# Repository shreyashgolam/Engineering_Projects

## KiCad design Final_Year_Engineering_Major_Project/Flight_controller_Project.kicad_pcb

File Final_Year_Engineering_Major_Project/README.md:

# Flight Controller PCB Design Using KiCad

## Project Overview
This project involves designing a **Flight Controller PCB** using **KiCad**. The PCB is intended for drone and UAV applications, providing essential functionalities like sensor integration, power management, and communication interfaces for flight control.

## System Architecture
The PCB consists of multiple modules interconnected for efficient data processing and motor control:

- **Microcontroller Unit (MCU)**:
  - STM32H753VITx (Flight Control Computer - FCC)
  - STM32F405RGTx (Navigation Computer - NAVC)
- **Power Management**:
  - 3.3V and 5V voltage regulators
  - Battery monitoring and current sensing (INA219AIDCNR)
  - Reverse polarity protection
- **Communication Interfaces**:
  - I2C, SPI, UART
  - USB debugging and programming
  - CAN bus (future expansion)
- **Sensor Integration**:
  - Inertial Measurement Unit (IMU) - BMI088
  - Magnetometer - IIS2MDCTR
  - Barometer - MPRLS0025PA00001A
  - GPS Receiver - u-blox MAX-8Q
  - Temperature Sensor - TMP100
- **Peripheral Control**:
  - PWM outputs for ESC/motor control
  - General-purpose GPIOs for expansion
  - Debugging LEDs and status indicators

## PCB Design
- **Schematic Files**:
  - `FCC.kicad_sch` - Flight Control Computer
  - `NAVC.kicad_sch` - Navigation Computer
  - `FCCPeripherals.kicad_sch` - Flight Control Peripherals
  - `NAVCPeripherals.kicad_sch` - Navigation Peripherals
  - `Power.kicad_sch` - Power Distribution
  - `Connections.kicad_sch` - Interconnects and external interfaces
- **PCB Layout File**:
  - `Flight_controller_Project.kicad_pcb`
- **Manufacturing Files**:
  - Gerber files and drill files for PCB fabrication
  - BOM (`.csv/.xml`) for component listing

## Workflow
1. **Schematic Design** – Define circuit connections in KiCad.
2. **PCB Layout** – Optimize routing and placement for minimal interference.
3. **Gerber File Generation** – Export necessary manufacturing files.
4. **Fabrication & Assembly** – Order PCBs and assemble components.
5. **Testing & Debugging** – Verify power, communication, and sensor readings.
6. **Firmware Development** – Program MCU for flight control operations.

## Applications
- Autonomous UAV and drone flight control
- GPS-based navigation systems
- Sensor fusion and real-time data processing
- Research and prototyping of flight stabilization algorithms

## Future Enhancements
- Implement CAN bus communication for robust inter-device connectivity.
- Integrate additional sensors for improved stability and performance.
- Develop an RF-based remote control module for manual override.
- Optimize power management for extended battery life.

This project provides a deep understanding of **flight electronics, embedded systems, and PCB design**.

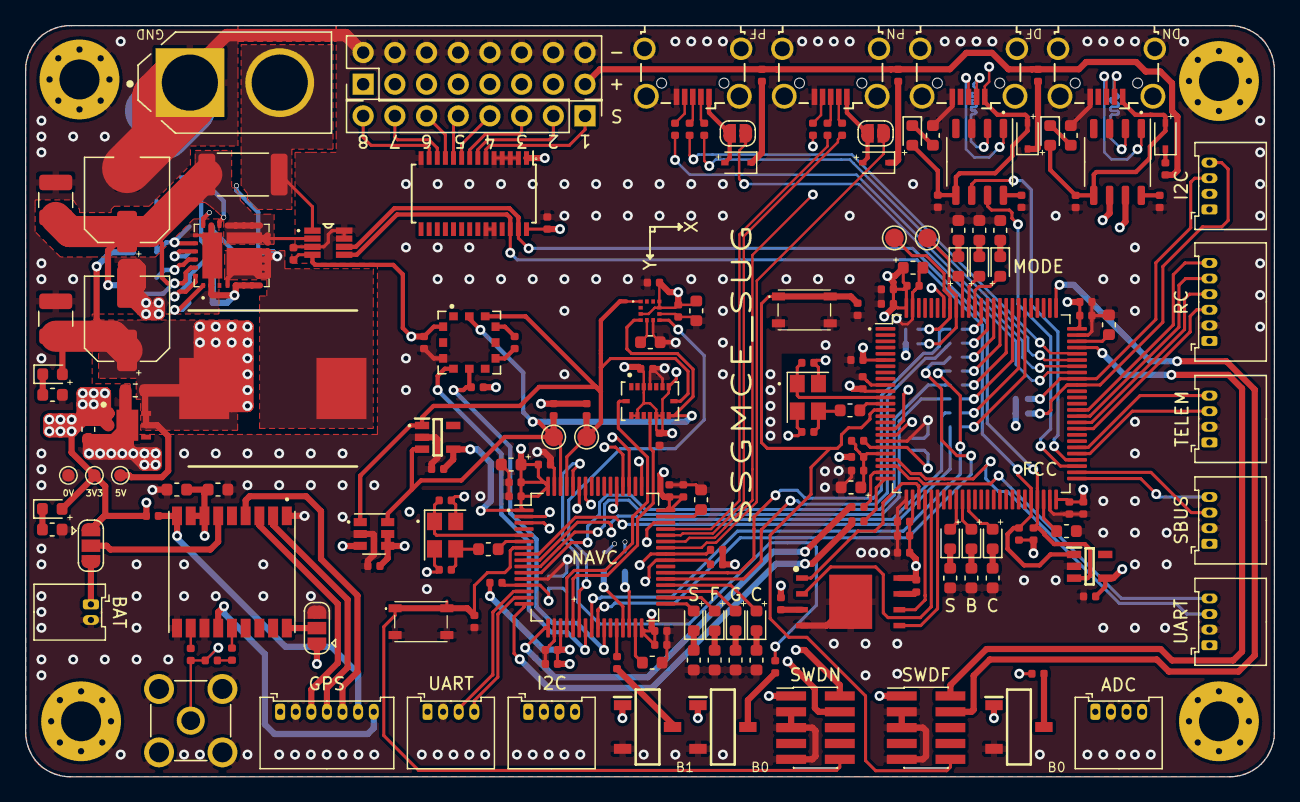
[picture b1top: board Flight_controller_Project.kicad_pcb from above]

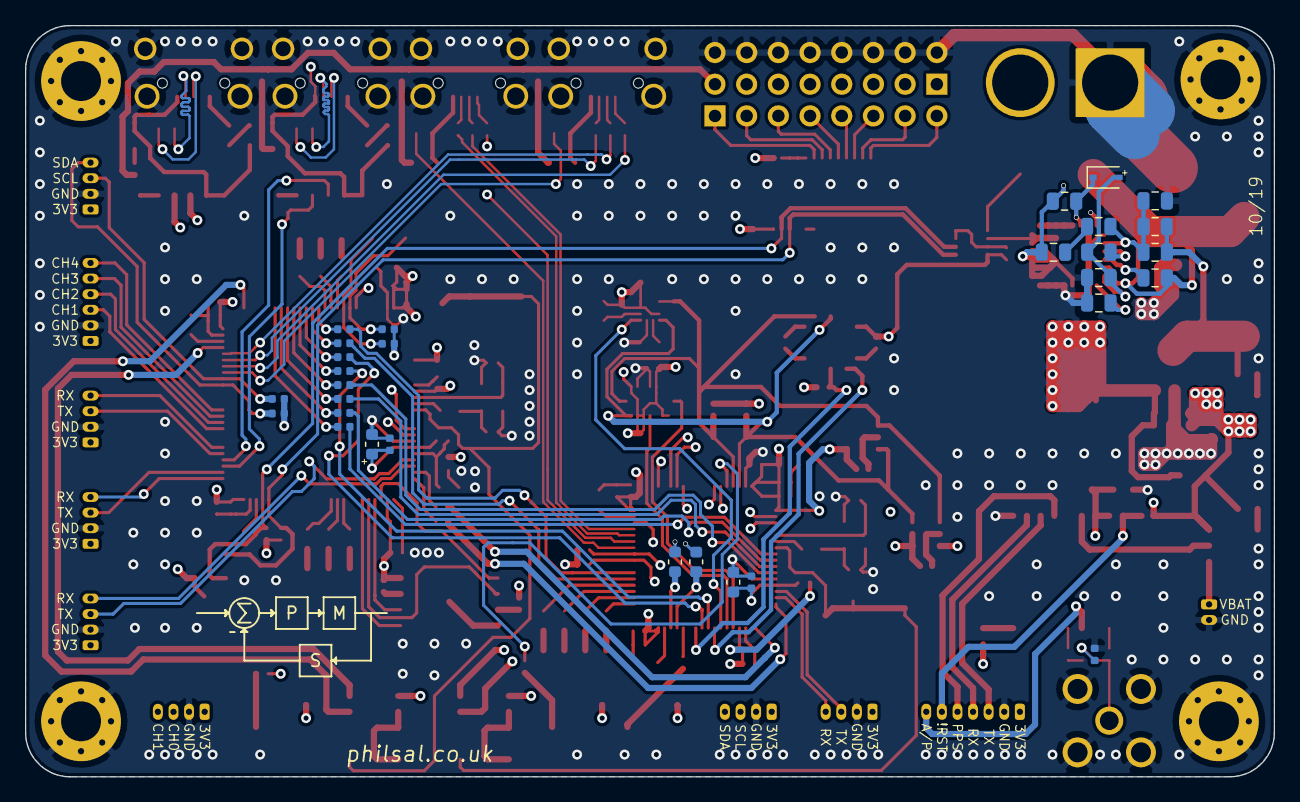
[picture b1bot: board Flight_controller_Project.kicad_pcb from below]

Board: 4 copper layers, 100.1 x 60.2 mm, 211 parts (30 on the bottom side), 174 nets.

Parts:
5V, 5V#2, 5V#3: TestPoint_Pad_D1.0mm
ADC: Conn_01x04; Molex_PicoBlade_53048-0410_1x04_P1.25mm_Horizontal
ANT1: 5-1814832-1; TE_5-1814832-1
BAT: Conn_01x02; Molex_PicoBlade_53048-0210_1x02_P1.25mm_Horizontal
BAT1: XT60-M; AMASS_XT60-M
C1, C8: 100u; C_Elec_6.3x7.7
C2, C9: 47u; C_1210_3225Metric
C3, C4: 2u2; C_0805_2012Metric
C5, C6: 100n; C_0805_2012Metric
C7: 4n7; C_0805_2012Metric
C10, C16, C17, C18, C19, C20, C21, C22, C23, C24, C25, C26, C28, C30, C31, C34, C35, C36, C40, C41, C42, C43, C44, C45, C46, C47, C48, C49, C51, C54, C55, C56, C58, C60, C61, C63, C68, C69, C70, C71: 100n; C_0402_1005Metric
C11, C12, C15, C39, C62: 10u; C_0603_1608Metric
C13, C14, C37, C38: 2u2; C_0603_1608Metric
C27, C29, C50, C64, C65: 1u; C_0603_1608Metric
C32, C33, C52, C53: 10p; C_0402_1005Metric
C57: 1n; C_0402_1005Metric
C59: 220n; C_0603_1608Metric
C66: 22p; C_0402_1005Metric
C67: 10n; C_0402_1005Metric
D1, D2, D3, D4, D5: SD103AWS; D_SOD-323
FB1, FB2, FB3, FB4, FB5, FB6: Ferrite_Bead_Small; L_0402_1005Metric
FCC: STM32H753VITx; LQFP-100_14x14mm_P0.5mm
GPS: Conn_01x07; Molex_PicoBlade_53048-0710_1x07_P1.25mm_Horizontal
HSE1, HSE2: 25MHz; Crystal_SMD_Abracon_ABM8G-4Pin_3.2x2.5mm
I2C, I2C#2: Conn_01x04; Molex_PicoBlade_53048-0410_1x04_P1.25mm_Horizontal
JP1, JP2: SolderJumper_2_Open; SolderJumper-2_P1.3mm_Open_RoundedPad1.0x1.5mm
JP3: SolderJumper_3_Open; SolderJumper-3_P1.3mm_Open_RoundedPad1.0x1.5mm
JP4: Jumper_3_Open; SolderJumper-3_P1.3mm_Open_RoundedPad1.0x1.5mm
L1: 15u; INDPM135125X650N
L2: 27n; L_0402_1005Metric
LED1, LED2, LED13, LED14: G; LED_0603_1608Metric
LED3, LED4, LED9, LED10: R; LED_0603_1608Metric
LED5, LED11: Y; LED_0603_1608Metric
LED6, LED7, LED8, LED12: B; LED_0603_1608Metric
NAVC: STM32F405RGTx; LQFP-64_10x10mm_P0.5mm
PWM_POW1: Conn_02x08_Odd_Even; PinHeader_2x08_P2.54mm_Vertical
PWM_SIG1: 2.54mm; PinHeader_1x08_P2.54mm_Vertical
R1: 0.01; R_2512_6332Metric
R2, R3: 10k; R_0805_2012Metric
R4: 19k6; R_0805_2012Metric
R5: 6k8; R_0805_2012Metric
R6: 1k3; R_0805_2012Metric
R7, R58, R59: 560; R_0603_1608Metric
R8: 240; R_0603_1608Metric
R9, R10, R11, R12, R13, R14, R28, R29, R30, R31: 4k7; R_0402_1005Metric
R15, R16, R17, R33, R34, R35: 330; R_0603_1608Metric
R18, R19, R20, R36: 100; R_0603_1608Metric
R21: 47; R_0402_1005Metric
R22, R24, R25, R26, R27, R37, R38: 10k; R_0402_1005Metric
R23, R32: 620; R_0603_1608Metric
R39, R40, R41, R42, R43, R44, R45, R46, R47, R48, R49: 10; R_0402_1005Metric
R50, R51: 0; R_0603_1608Metric
R52, R53, R55, R56: 22; R_0402_1005Metric
R54, R57: 560; R_0402_1005Metric
RC: Conn_01x06; Molex_PicoBlade_53048-0610_1x06_P1.25mm_Horizontal
REG1: MIC26903YJL-TR; MIC24054YJLTR
REG2: LD39200PU33R; SON95P300X300X100-7N-D
SBUS: Conn_01x04; Molex_PicoBlade_53048-0410_1x04_P1.25mm_Horizontal
SW1, SW5: SKRPANE010; SKRPADE010
SW2, SW3, SW4: TDD01H0SB1R; SOT175P420X230-3N
SWDF: Conn_02x05_Odd_Even; PinHeader_2x05_P1.27mm_Vertical_SMD
SWDN: Conn_02x05_Odd_Even; PinHeader_2x05_P1.27mm_Vertical_SMD
TELEM: Conn_01x04; Molex_PicoBlade_53048-0410_1x04_P1.25mm_Horizontal
TP1, TP2, TP3, TP4: I2C1; TestPoint_Pad_D1.5mm
U1: INA219AIDCNR; SOT65P280X145-8N
U2: PCA9685PW; TSSOP-28_4.4x9.7mm_P0.65mm
U3, U9: 24CW1280T-I_OT; SOT95P280X145-5N
U4: W25N01GVZEIG_TR; SON127P800X600X80-9N-D
U5: BMI088; PQFN50P450X300X100-16N
U6: TMP100; SOT-23-6
U7: MPRLS0025PA00001A; XDCR_MPRLS0025PA00001A
U8: IIS2MDCTR
U10: u-blox MAX-8Q; GPS18P-SMD-1.1-10X9.6MM
U11, U12: otter:CH330; SSOP-8_3.9x5.05mm_P1.27mm
UART: Conn_01x04; Molex_PicoBlade_53048-0410_1x04_P1.25mm_Horizontal
UART#2: Conn_01x04; Molex_PicoBlade_53048-0410_1x04_P1.25mm_Horizontal
USB1, USB2, USB3, USB4: USB_B_Micro; USB_Micro-B_Wuerth_629105150521_CircularHoles

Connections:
+3V3: 5V#2.1, ADC.1, C10.1, C12.1, C15.1, C16.1, C17.1, C18.1, C19.1, C20.1, C21.1, C22.1, C23.1, C24.1, C25.1, C26.1, C34.1, C35.1, C36.2, C39.1, C40.1, C41.1, C42.1, C43.1, C44.1, C45.1, C46.1, C47.1, C48.1, C54.1, C55.1, C56.1, C58.1, C60.1, C61.1, C62.1, C63.1, C64.1, C65.1, FB1.2, FB2.2, FCC.6, FCC.11, FCC.27, FCC.50, FCC.75, FCC.100, GPS.1, I2C.1, I2C#2.1, JP3.1, JP4.1, LED2.2, NAVC.1, NAVC.19, NAVC.32, NAVC.48, NAVC.64, R9.1, R10.1, R11.1, R12.1, R13.1, R14.1, R24.1, R25.1, R28.1, R29.1, R30.1, R31.1, R37.1, R38.1, RC.1, REG2.1, REG2.2, SBUS.1, SW2.1, SW3.1, SW4.1, SWDF.1, SWDN.1, TELEM.1, U1.4, U2.1, U2.28, U3.4, U4.8, U5.3, U5.7, U5.10, U5.11, U5.14, U5.15, U6.3, U6.4, U6.5, U7.12, U8.3, U8.9, U8.10, U9.4, U10.7, U10.8, UART.1, UART#2.1
+5V: 5V.1, C7.1, C8.1, C9.1, C11.1, FB3.1, FB4.1, FB5.1, FB6.1, L1.2, LED1.2, PWM_POW1.1, PWM_POW1.3, PWM_POW1.5, PWM_POW1.7, PWM_POW1.9, PWM_POW1.11, PWM_POW1.13, PWM_POW1.15, R5.1, REG2.5, REG2.6
ADC3_0_FCC: ADC.3, FCC.17
ADC3_1_FCC: ADC.4, FCC.18
BAR_NRST_NAVC: NAVC.26, R37.2, U7.8
BOOT0_FCC: FCC.94, R22.2
BOOT0_NAVC: NAVC.60, R26.2
BOOT1_NAVC: NAVC.28, R27.2
GND: 5V#3.1, ADC.2, ANT1.2, ANT1.3, ANT1.4, ANT1.5, BAT.2, BAT1.1, C1.2, C2.2, C3.2, C4.2, C8.2, C9.2, C10.2, C11.2, C12.2, C13.2, C14.2, C15.2, C16.2, C17.2, C18.2, C19.2, C20.2, C21.2, C22.2, C23.2, C24.2, C25.2, C26.2, C27.2, C28.2, C29.2, C30.2, C31.2, C32.2, C33.2, C34.2, C35.2, C36.1, C37.2, C38.2, C39.2, C40.2, C41.2, C42.2, C43.2, C44.2, C45.2, C46.2, C47.2, C48.2, C49.2, C50.2, C51.2, C52.2, C53.2, C54.2, C55.2, C56.2, C58.2, C59.2, C60.2, C61.2, C62.2, C63.2, C64.2, C65.2, C67.2, C68.1, C69.1, C70.1, C71.1, FCC.10, FCC.19, FCC.26, FCC.49, FCC.74, FCC.99, GPS.2, HSE1.2, HSE1.4, HSE2.2, HSE2.4, I2C.2, I2C#2.2, JP3.3, NAVC.12, NAVC.18, NAVC.63, PWM_POW1.2, PWM_POW1.4, PWM_POW1.6, PWM_POW1.8, PWM_POW1.10, PWM_POW1.12, PWM_POW1.14, PWM_POW1.16, R6.1, R7.1, R8.1, R15.1, R16.1, R17.1, R18.1, R19.1, R20.1, R33.1, R34.1, R35.1, R36.1, R58.1, R59.1, RC.2, REG1.2, REG1.5, REG1.6, REG1.7, REG1.8, REG1.21, REG1.23, REG1.31, REG2.3, REG2.7, SBUS.2, SW1.3, SW1.4, SW2.2, SW3.2, SW4.2, SW5.3, SW5.4, SWDF.3, SWDF.5, SWDF.9, SWDN.3, SWDN.5, SWDN.9, TELEM.2, U1.3, U1.7, U1.8, U2.2, U2.3, U2.4, U2.5, U2.14, U2.23, U2.24, U3.2, U4.4, U4.9, U5.4, U5.6, U6.2, U7.10, U8.6, U8.8, U9.2, U10.1, U10.10, U10.12, U11.3, U12.3, UART.2, UART#2.2, USB1.5, USB1.6, USB2.5, USB2.6, USB3.5, USB3.6, USB4.5, USB4.6
GPIO_A_FCC: FCC.81, R40.2
GPIO_A_NAVC: NAVC.8, R40.1
GPIO_B_FCC: FCC.82, R41.2
GPIO_B_NAVC: NAVC.9, R41.1
GPIO_C_FCC: FCC.83, R42.2
GPIO_C_NAVC: NAVC.10, R42.1
GPIO_D_FCC: FCC.84, R43.2
GPIO_D_NAVC: NAVC.11, R43.1
GPIO_E_FCC: FCC.85, R44.2
GPIO_E_NAVC: NAVC.24, R44.1
GPIO_F_FCC: FCC.86, R45.2
GPIO_F_NAVC: NAVC.25, R45.1
GPIO_G_FCC: FCC.87, R46.2
GPIO_G_NAVC: NAVC.37, R46.1
GPIO_H_FCC: FCC.88, R47.2
GPIO_H_NAVC: NAVC.38, R47.1
GPS_BAT_BACKUP: JP4.2, U10.6
GPS_LNA_EN_NAVC: GPS.7, NAVC.2, U10.13
GPS_NRST_NAVC: GPS.6, NAVC.3, R38.2, U10.9
GPS_PPS_NAVC: GPS.5, NAVC.53, U10.4
HSE_IN_FCC: C32.1, FCC.12, HSE1.1
HSE_IN_NAVC: C52.1, HSE2.1, NAVC.5
HSE_OUT_FCC: FCC.13, R23.1
HSE_OUT_NAVC: NAVC.6, R32.1
I2C1_SCL_FCC: FCC.92, R9.2, R50.2, TP1.1
I2C1_SCL_NAVC: NAVC.61, R28.2, TP3.1, U5.8, U6.1, U7.3, U8.1, U9.1
I2C1_SDA_FCC: FCC.93, R10.2, R51.2, TP2.1
I2C1_SDA_NAVC: NAVC.62, R29.2, TP4.1, U5.9, U6.6, U7.2, U8.4, U9.3
I2C2_SCL_FCC: FCC.46, R11.2, U1.5, U2.26, U3.1
I2C2_SCL_NAVC: NAVC.29, R50.1
I2C2_SDA_FCC: FCC.47, R12.2, U1.6, U2.27, U3.3
I2C2_SDA_NAVC: NAVC.30, R51.1
I2C3_SCL_FCC: FCC.67, I2C.3, R13.2
I2C3_SCL_NAVC: I2C#2.3, NAVC.41, R30.2
I2C3_SDA_FCC: FCC.66, I2C.4, R14.2
I2C3_SDA_NAVC: I2C#2.4, NAVC.40, R31.2
INT_ACC_NAVC: NAVC.20, U5.16
INT_BAR_NAVC: NAVC.23, U7.9
INT_GYR_NAVC: NAVC.21, U5.12
INT_MAG_NAVC: NAVC.22, U8.7
LED_A_FCC: FCC.34, LED3.2
LED_A_NAVC: LED9.2, NAVC.33
LED_B_FCC: FCC.35, LED4.2
LED_B_NAVC: LED10.2, NAVC.34
LED_C_FCC: FCC.36, LED5.2
LED_C_NAVC: LED11.2, NAVC.35
LED_D_FCC: FCC.89, LED6.2
LED_D_NAVC: LED12.2, NAVC.36
LED_E_FCC: FCC.90, LED7.2
LED_F_FCC: FCC.91, LED8.2
NRST_FCC: C31.1, FCC.14, SW1.1, SW1.2, SWDF.10
NRST_NAVC: C49.1, NAVC.7, SW5.1, SW5.2, SWDN.10
unnamed: ANT1.1, C66.1, C67.1, L2.2
unnamed: C3.1, REG1.1
unnamed: C4.1, D1.2, R3.2, REG1.28
unnamed: C6.2, R4.1
unnamed: C13.1, FCC.48
unnamed: C14.1, FCC.73
unnamed: C33.1, HSE1.3, R23.2
unnamed: C37.1, NAVC.31
unnamed: C38.1, NAVC.47
unnamed: C53.1, HSE2.3, R32.2
unnamed: C57.1, U7.6
unnamed: C57.2, U7.4
unnamed: C59.1, U8.5
unnamed: C66.2, U10.11
unnamed: C68.2, D4.2, LED13.2, U11.5, USB3.1
unnamed: C69.2, U11.8
unnamed: C70.2, D5.2, LED14.2, U12.5, USB4.1
unnamed: C71.2, U12.8
unnamed: D2.1, FB3.2
unnamed: D2.2, JP1.1, USB1.1
unnamed: D3.1, FB4.2
unnamed: D3.2, JP2.1, USB2.1
unnamed: D4.1, FB5.2
unnamed: D5.1, FB6.2
unnamed: BAT.1, JP4.3
unnamed: JP3.2, U10.18
unnamed: L2.1, R39.1
unnamed: LED1.1, R7.2
unnamed: LED2.1, R8.2
unnamed: LED3.1, R15.2
unnamed: LED4.1, R16.2
unnamed: LED5.1, R17.2
unnamed: LED6.1, R18.2
unnamed: LED7.1, R19.2
unnamed: LED8.1, R20.2
unnamed: LED9.1, R33.2
unnamed: LED10.1, R34.2
unnamed: LED11.1, R35.2
unnamed: LED12.1, R36.2
unnamed: LED13.1, R58.2
unnamed: LED14.1, R59.2
unnamed: R22.1, SW2.3
unnamed: R24.2, U4.7
unnamed: R25.2, U4.3
unnamed: R26.1, SW3.3
unnamed: R27.1, SW4.3
unnamed: R39.2, U10.14
unnamed: R52.2, USB1.3
unnamed: R53.2, USB1.2
unnamed: R54.2, USB1.4
unnamed: R55.2, USB2.3
unnamed: R56.2, USB2.2
unnamed: R57.2, USB2.4
unnamed: U11.1, USB3.3
unnamed: U11.2, USB3.2
unnamed: U12.1, USB4.3
unnamed: U12.2, USB4.2
PWM_0: PWM_SIG1.1, U2.6
PWM_1: PWM_SIG1.2, U2.7
PWM_2: PWM_SIG1.3, U2.8
PWM_3: PWM_SIG1.4, U2.9
PWM_4: PWM_SIG1.5, U2.10
PWM_5: PWM_SIG1.6, U2.11
PWM_6: PWM_SIG1.7, U2.12
PWM_7: PWM_SIG1.8, U2.13
REG_BST: C5.2, D1.1, REG1.20
REG_CS: C5.1, C6.1, L1.1, REG1.4, REG1.9, REG1.10, REG1.11, REG1.12, REG1.22, REG1.29
REG_EN: R2.2, REG1.26
REG_FB: C7.2, R4.2, R5.2, R6.2, REG1.24
REG_PG: R3.1, REG1.25
REG_VIN: C1.1, C2.1, R1.1, R2.1, REG1.13, REG1.14, REG1.15, REG1.16, REG1.17, REG1.18, REG1.19, REG1.27, REG1.30, U1.2
SPI1_CS_FLASH_FCC: FCC.28, U4.1
SPI1_MISO_FCC: FCC.30, U4.2
SPI1_MOSI_FCC: FCC.31, U4.5
SPI1_SCK_FCC: FCC.29, U4.6
SWCLK_FCC: FCC.76, SWDF.4
SWCLK_NAVC: NAVC.49, SWDN.4
SWDIO_FCC: FCC.72, SWDF.2
SWDIO_NAVC: NAVC.46, SWDN.2
TIM4_CH1_FCC: FCC.59, RC.3
TIM4_CH2_FCC: FCC.60, RC.4
TIM4_CH3_FCC: FCC.61, RC.5
TIM4_CH4_FCC: FCC.62, RC.6
UART1_RX_FCC: FCC.54, U11.6
UART1_RX_NAVC: GPS.4, NAVC.59, U10.2
UART1_TX_FCC: FCC.53, U11.7
UART1_TX_NAVC: GPS.3, NAVC.58, U10.3
UART2_RX_FCC: FCC.25, R48.2
UART2_RX_NAVC: NAVC.17, R49.1
UART2_TX_FCC: FCC.24, R49.2
UART2_TX_NAVC: NAVC.16, R48.1
UART3_RX_FCC: FCC.56, TELEM.4
UART3_RX_NAVC: NAVC.52, U12.6
UART3_TX_FCC: FCC.55, TELEM.3
UART3_TX_NAVC: NAVC.51, U12.7
UART4_RX_FCC: FCC.23, UART#2.4
UART4_RX_NAVC: NAVC.15, UART.4
UART4_TX_FCC: FCC.22, UART#2.3
UART4_TX_NAVC: NAVC.14, UART.3
UART5_RX_FCC: FCC.51, SBUS.4
UART5_TX_FCC: FCC.52, SBUS.3
USB_DM_FCC: FCC.70, R53.1
USB_DM_NAVC: NAVC.44, R56.1
USB_DP_FCC: FCC.71, R52.1
USB_DP_NAVC: NAVC.45, R55.1
USB_ID_FCC: FCC.69, R54.1
USB_ID_NAVC: NAVC.43, R57.1
USB_VBUS_FCC: FCC.68, JP1.2
USB_VBUS_NAVC: JP2.2, NAVC.42
VDDA_FCC: C27.1, C28.1, FB1.1, FCC.21, R21.2
VDDA_NAVC: C50.1, C51.1, FB2.1, NAVC.13
VIN+: BAT1.2, R1.2, U1.1
VREF+_FCC: C29.1, C30.1, FCC.20, R21.1

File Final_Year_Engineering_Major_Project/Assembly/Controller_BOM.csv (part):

Ref Des,Qty,Manufacturer,Mfr Part #,Value,Package,Type,Your Instructions / Notes
ANT1,1,TE Connectivity,5-1814832-1,5-1814832-1,5-1814832-1:TE_5-1814832-1,THT,"50 Ohm SMA, see 3D picture for orientation"
BAT1,1,SparkFun,PRT-10474,XT60-M,XT60-M:AMASS_XT60-M,THT,"Male XT-60 Connector, NEGATIVE TERMINAL indicated by DOT on silkscreen, SEE 3D PICTURE FOR REFERENCE!"
"C1, C8",2,Panasonic,EEE-FPV101XAV,100u,Capacitor_SMD:C_Elec_6.3x7.7,SMD,"Low ESR, High Ripple Current, Al Electrolytic, 35V, Polarity indicated by + on silkscreen"
"C2, C9",2,Taiyo Yuden,GMK325BJ226MM-T,22u,Capacitor_SMD:C_1210_3225Metric,SMD,"Low ESR, 35V"
"C3, C4",2,KEMET,C0805C225K4REC7210,2u2,Capacitor_SMD:C_0805_2012Metric,SMD,at least 10V rated
"C5, C6",2,KEMET,C0805X104K5RAC3316,100n,Capacitor_SMD:C_0805_2012Metric,SMD,at least 10V rated
C7,1,KEMET,C0805C472J3GEC7210,4n7,Capacitor_SMD:C_0805_2012Metric,SMD,at least 10V rated
"C10, C16, C17, C18, C19, C20, C21, C22, C23, C24, C25, C26, C28, C30, C31, C34, C35, C36, C40, C41, C42, C43, C44, C45, C46, C47, C48, C49, C51, C54, C55, C56, C58, C60, C61, C63, C68, C69, C70, C71, ",40,Murata Electronics,GRM155R61H104JE14D,100n,Capacitor_SMD:C_0402_1005Metric,SMD,at least 10V rated
"C11, C12, C62",3,Murata Electronics,GRM188R61E106KA73D,10u,Capacitor_SMD:C_0603_1608Metric,SMD,at least 10V rated
"C15, C39",2,AVX,F381A106MMAAH1,10u,Capacitor_SMD:C_0603_1608Metric,SMD,"Tantalum, Polarity indicated by + on silkscreen"
"C13, C14,  C37, C38,",4,Yageo,CC0603KRX5R9BB225,2u2,Capacitor_SMD:C_0603_1608Metric,SMD,ESR < 100mOhms!
"C27, C29, C50",3,AVX,TACL105K010RTA,1u,Capacitor_SMD:C_0603_1608Metric,SMD,"Tantalum, Polarity indicated by + on silkscreen"
"C64, C65",2,KEMET,C0603C105Z3VACTU,1u,Capacitor_SMD:C_0603_1608Metric,SMD,at least 10V rated
"C32, C33, C52, C53, ",4,AVX,04025A100JAT2A,10p,Capacitor_SMD:C_0402_1005Metric,SMD,at least 10V rated
"C57, ",1,KEMET,C0402C102J5GAC7411,1n,Capacitor_SMD:C_0402_1005Metric,SMD,at least 10V rated
"C59, ",1,KEMET,C0603C224K4RAC7411,220n,Capacitor_SMD:C_0603_1608Metric,SMD,at least 10V rated
C66,1,KEMET,C0402C220J8GACTU,22p,Capacitor_SMD:C_0402_1005Metric,SMD,at least 10V rated
"C67, ",1,KEMET,C0402C103J3RACAUTO,10n,Capacitor_SMD:C_0402_1005Metric,SMD,at least 10V rated
"D1, D2, D3, D5, D4, ",5,Diodes Incorporated,SD103AWS-7-F,SD103AWS,Diode_SMD:D_SOD-323,SMD,"Schottky diode, Polarity indicated by + on silkscreen"
"FB1, FB2, FB3, FB4, FB5, FB6, ",6,TDK,MPZ1005S121HT000,Ferrite_Bead_Small,Inductor_SMD:L_0402_1005Metric,SMD,"Ferrite bead, 1.5A current rating"
"FCC1, ",1,STMicroelectronics,STM32H753VIT6,STM32H753VITx,Package_QFP:LQFP-100_14x14mm_P0.5mm,SMD,"Pin 1 indicated by DOT on silkscreen, WATCH FOR PIN 1 ON DATASHEET (LQFP-100)"
"GPS_BAT1, ",1,Molex,53048-0210,Conn_01x02,Connector_Molex:Molex_PicoBlade_53048-0210_1x02_P1.25mm_Horizontal,THT,Watch orientation! See attached 3D picture!
"GPS_NAVC1, ",1,Molex,53048-0710,Conn_01x07,Connector_Molex:Molex_PicoBlade_53048-0710_1x07_P1.25mm_Horizontal,THT,Watch orientation! See attached 3D picture!
"HSE1, HSE2",2,ABRACON,ABM8G-25.000MHZ-4Y-T3,25MHz,Crystal:Crystal_SMD_Abracon_ABM8G-4Pin_3.2x2.5mm,SMD,"Pin 1 indicated by DOT on silkscreen, WATCH FOR PIN 1 ON DATASHEET"
L1,1,Bourns,SRP1265A-150M,15u,SRP1265A-150M:INDPM135125X650N,SMD,DC Current Rating at least 9A
L2,1,Murata Electronics,LQW15AN27NJ8ZD,27n,Inductor_SMD:L_0402_1005Metric,SMD,
"LED1, LED2, LED13, LED14, ",4,Dialight,599-0081-007F,GREEN,LED_SMD:LED_0603_1608Metric,SMD,"Green LED, Polarity indicated by + on silkscreen"
"LED3, LED4, LED9, LED10, ",4,Dialight,599-0010-007F,RED,LED_SMD:LED_0603_1608Metric,SMD,"Red LED, Polarity indicated by + on silkscreen"
"LED5, LED11, ",2,Dialight,599-0040-007F,YELLOW,LED_SMD:LED_0603_1608Metric,SMD,"Yellow LED, Polarity indicated by + on silkscreen"
"LED6, LED7, LED8, LED12, ",4,Dialight,599-0091-007F,BLUE,LED_SMD:LED_0603_1608Metric,SMD,"Blue LED, Polarity indicated by + on silkscreen"
"NAVC1, ",1,STMicroelectronics,STM32F405RGT6,STM32F405RGTx,Package_QFP:LQFP-64_10x10mm_P0.5mm,SMD,"Pin 1 indicated by DOT on silkscreen, WATCH FOR PIN 1 ON DATASHEET (LQFP-64)"
"PWM_POW1, ",1,Samtec,HTSW-108-07-T-T,Conn_02x08_Odd_Even,Connector_PinHeader_2.54mm:PinHeader_2x08_P2.54mm_Vertical,THT,"3 Rows 8 Columns (24 Positions total), 2.54mm Pitch, Vertical Male Header Pins"
"R1, ",1,Yageo,PE2512FKE7W0R01Z,0.01,Resistor_SMD:R_2512_6332Metric,SMD,1W 1% 10mOhms 2512 Current Sense Resistor
"R2, R3, ",2,Panasonic,ERJ-T06J103V,10k,Resistor_SMD:R_0805_2012Metric,SMD,1/4W
"R4, ",1,Panasonic,ERJ-PB6B1962V,19k6,Resistor_SMD:R_0805_2012Metric,SMD,"1%, 1/8W"
"R5, ",1,KOA Speer,RK73H2ATTD6R80F,6k8,Resistor_SMD:R_0805_2012Metric,SMD,"1%, 1/8W"
"R6, ",1,KOA Speer,RK73H2ATTD1301F,1k3,Resistor_SMD:R_0805_2012Metric,SMD,"1%, 1/8W"
"R7, R58, R59, ",3,Panasonic,ERJ-PA3F5600V,560,Resistor_SMD:R_0603_1608Metric,SMD,1/4W
"R8, ",1,Panasonic,ERJ-PA3F2400V,240,Resistor_SMD:R_0603_1608Metric,SMD,1/4W
"R9, R10, R11, R12, R13, R14, R28, R29, R30, R31, ",10,KOA Speer,SG73P1ETTP4701F,4k7,Resistor_SMD:R_0402_1005Metric,SMD,1/4W
"R15, R16, R17, R33, R34, R35, ",6,Panasonic,ERJ-PA3D3300V,330,Resistor_SMD:R_0603_1608Metric,SMD,1/4W
"R18, R19, R20, R36, ",4,Panasonic,ERJ-PA3D1000V,100,Resistor_SMD:R_0603_1608Metric,SMD,1/4W
"R21, ",1,Panasonic,ERA-2AED470X,47,Resistor_SMD:R_0402_1005Metric,SMD,1/8W
"R22, R24, R25, R26, R27, R37, R38, ",7,TE Connectivity / Holsworthy,CRGP0402F10K,10k,Resistor_SMD:R_0402_1005Metric,SMD,1/4W
"R23, R32, ",2,Panasonic,ERJ-PA3F6200V,620,Resistor_SMD:R_0603_1608Metric,SMD,1/4W
"R39, R40, R41, R42, R43, R44, R45, R46, R47, R48, R49, ",11,Panasonic,ERA-2AKD100X,10,Resistor_SMD:R_0402_1005Metric,SMD,1/8W
"R50, R51, ",2,Vishay / Dale,RCS06030000Z0EC,0,Resistor_SMD:R_0603_1608Metric,SMD,1/8W
"R52, R53, R55, R56, ",4,Panasonic,ERA-2AKD220X,22,Resistor_SMD:R_0402_1005Metric,SMD,1/8W
"R54, R57, ",2,TE Connectivity / Holsworthy,CRGP0402F560R,560,Resistor_SMD:R_0402_1005Metric,SMD,1/8W
"RCIN_FCC1, ",1,Molex,53048-0610,Conn_01x06,Connector_Molex:Molex_PicoBlade_53048-0610_1x06_P1.25mm_Horizontal,THT,Watch orientation! See attached 3D picture!
"REG1, ",1,Microchip Technology,MIC26903YJL-TR,MIC26903YJL-TR,MLF-28,SMD,Pin 1 indicated by DOT on silkscreen
"REG2, ",1,STMicroelectronics,LD39200PU33R,LD39200PU33R,DFN-6,SMD,Pin 1 indicated by DOT on silkscreen
"SW1, SW5, ",2,ALPS,SKRPANE010,SKRPANE010,SKRPANE010:SKRPADE010,SMD,See attached 3D picture for orientation
"SW2, SW3, SW4, ",3,C&K,TDD01H0SB1R,TDD01H0SB1R,TDD01H0SB1R:SOT175P420X230-3N,SMD,See attached 3D picture for orientation
"SWD1, SWD2, ",2,Harwin,M50-3600542R,Conn_02x05_Odd_Even,Connector_PinHeader_1.27mm:PinHeader_2x05_P1.27mm_Vertical_SMD,SMD,"2 Rows, 5 Columns (10 Positions), SMD 1.27mm pitch, See attached 3D picture for orientation"
"U1, ",1,Texas Instruments,INA219AIDCNR,INA219AIDCNR,SOT-23-8,SMD,Pin 1 indicated by DOT on silkscreen
"U2, ",1,NXP Semiconductors,"PCA9685PW,118",PCA9685PW,TSSOP28,SMD,Pin 1 indicated by DOT on silkscreen
"U3, U9, ",2,Microchip Technology,24CW1280T-I/OT,24CW1280T-I_OT,SOT-23-5,SMD,Pin 1 indicated by DOT on silkscreen
"U4, ",1,Winbond,W25N01GVZEIG TR,W25N01GVZEIG_TR,WSON 8x6-mm ,SMD,Pin 1 indicated by DOT on silkscreen
"U5, ",1,Bosch Sensortec,BMI088,BMI088,LGA-16,SMD,Pin 1 indicated by DOT on silkscreen
"U6, ",1,Texas Instruments,TMP100NA/3K,TMP100,SOT-23-6,SMD,Pin 1 indicated by DOT on silkscreen
"U7, ",1,Honeywell,MPRLS0025PA00001A,MPRLS0025PA00001A,MPRLS0025PA00001A:XDCR_MPRLS0025PA00001A,SMD,Pin 1 indicated by DOT on silkscreen
"U8, ",1,STMicroelectronics,IIS2MDCTR,IIS2MDCTR,LGA-12 2.0 x 2.0 x 0.7 mm,SMD,Pin 1 indicated by DOT on silkscreen
"U10, ",1,u-blox,MAX-8Q,u-blox MAX-8Q,MODULE-GPS-SMD-MAX-7Q-0_18P-9.6X10MM_:GPS18P-SMD-1.1-10X9.6MM,SMD,"Pin 1 indicated by DOT on silkscreen, Datasheet: https://www.u-blox.com/sites/default/files/MAX-8_DataSheet_%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"
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
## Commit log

2025-02-04 Final Year Engineering Major Project
2025-02-04 Engineering Minor Projects
2025-02-04 Engineering Minor Project Arduino UNO R3 PCB Design
2025-02-16 Engineering Major Project
2025-02-16 Deleted old version Flight Controller
2025-02-16 Engineering Minor Project Arduino UNO R3
2025-02-16 Engineering Minor Project Arduino UNO R3 Design
2025-02-16 Deleted older version files
